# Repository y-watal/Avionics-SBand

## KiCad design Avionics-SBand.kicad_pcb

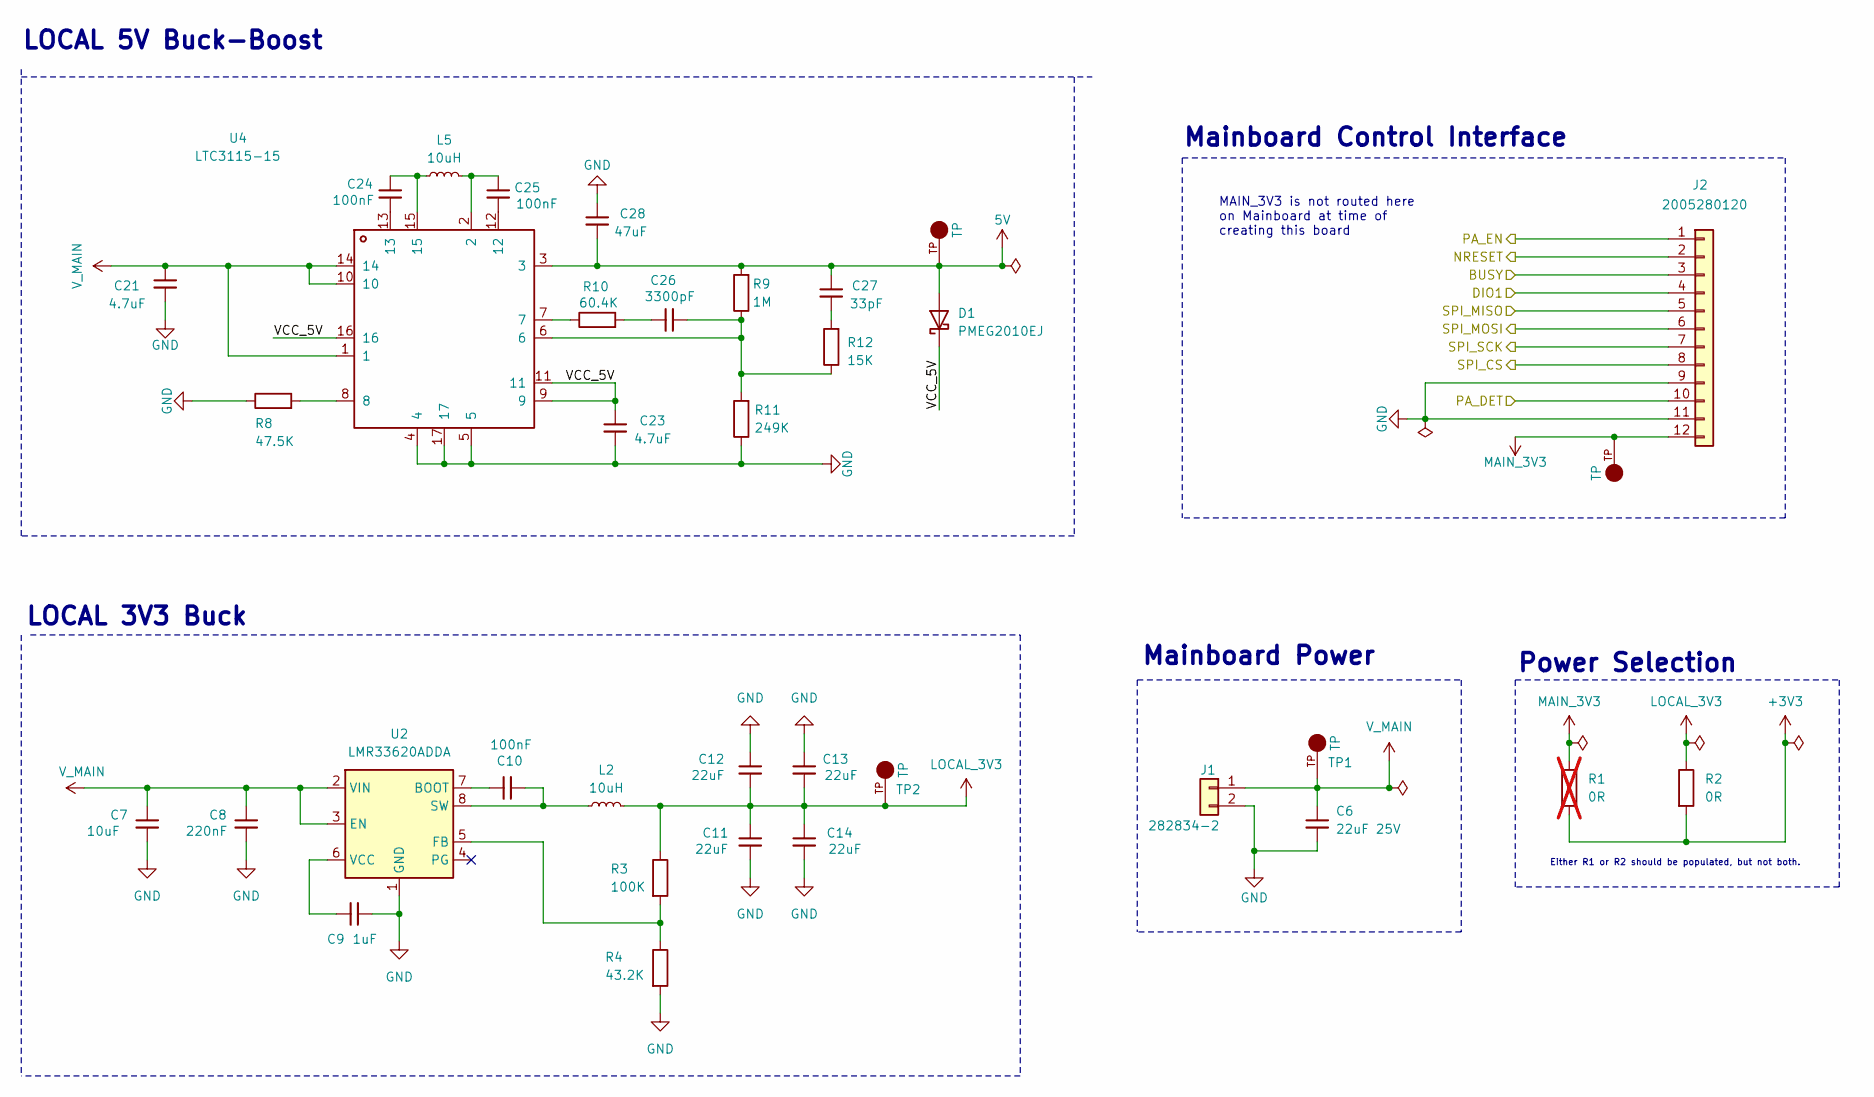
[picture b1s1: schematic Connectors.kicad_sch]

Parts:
C6: 22uF 25V; C_1210_3225Metric
C7: 10uF; C_1210_3225Metric
C8: 220nF; C_0603_1608Metric
C9: 1uF; C_0603_1608Metric
C10, C24, C25: 100nF; C_0603_1608Metric
C11, C12, C13, C14: 22uF; C_1206_3216Metric
C21, C23: 4.7uF; C_0603_1608Metric
C26: 3300pF; C_0603_1608Metric
C27: 33pF; C_0603_1608Metric
C28: 47uF; C_1206_3216Metric
D1: PMEG2010EJ; D_SOD-323F
J1: 282834-2; TE_282834-2; MPN 282834-2; Digikey PN A98333-ND
J2: 2005280120; Molex_200528-0120_1x12-1MP_P1.00mm_Horizontal
L2, L5: 10uH; L_Bourns_SRP7028A_7.3x6.6mm
R1: 0R; R_1206_3216Metric; not fitted
R2: 0R; R_1206_3216Metric
R3: 100K; R_0603_1608Metric
R4: 43.2K; R_0603_1608Metric
R8: 47.5K; R_0603_1608Metric
R9: 1M; R_0603_1608Metric
R10: 60.4K; R_0603_1608Metric
R11: 249K; R_0603_1608Metric
R12: 15K; R_0603_1608Metric
TP1, TP2, TP10, TP17: TP; KEYSTONE_5001; MPN 5001; Digikey PN 36-5001-ND
U2: LMR33620ADDA; Texas_HSOP-8-1EP_3.9x4.9mm_P1.27mm_ThermalVias
U4: LTC3115-15; DFN-16-1EP_4x5mm_P0.5mm_EP2.44x4.34mm

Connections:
5V: C27.1, C28.1, D1.2 (A), R9.2, TP10.TP, U4.3; also elsewhere on the board
+3V3: R1.2, R2.2; also elsewhere on the board
/Connectors/VCC_5V: C23.1, D1.1 (K), U4.9, U4.11, U4.16
/PA_to_Antenna/PA_DET: J2.10; also elsewhere on the board
/PA_to_Antenna/PA_EN: J2.1; also elsewhere on the board
/SX1280/BUSY: J2.3; also elsewhere on the board
/SX1280/DIO1: J2.4; also elsewhere on the board
/SX1280/NRESET: J2.2; also elsewhere on the board
/SX1280/SPI_CS: J2.8; also elsewhere on the board
/SX1280/SPI_MISO: J2.5; also elsewhere on the board
/SX1280/SPI_MOSI: J2.6; also elsewhere on the board
/SX1280/SPI_SCK: J2.7; also elsewhere on the board
GND: C6.2, C7.1, C8.1, C9.1, C11.1, C12.1, C13.1, C14.1, C21.1, C23.2, C28.2, J1.2, J2.9, J2.11, R4.2, R8.1, R11.1, U2.1 (GND), U2.9 (GND), U4.4, U4.5, U4.17; also elsewhere on the board
LOCAL_3V3: C11.2, C12.2, C13.2, C14.2, L2.2, R2.1, R3.1, TP2.TP
MAIN_3V3: J2.12, R1.1, TP17.TP
unnamed: C24.1, U4.13
unnamed: C24.2, L5.1, U4.15
unnamed: C25.1, L5.2, U4.2
unnamed: C25.2, U4.12
unnamed: C26.1, R10.2
unnamed: C26.2, R9.1, R11.2, R12.1, U4.6
unnamed: C27.2, R12.2
unnamed: R8.2, U4.8
unnamed: R10.1, U4.7
unnamed: C10.1, U2.7 (BOOT)
unnamed: R3.2, R4.1, U2.5 (FB)
unnamed: C10.2, L2.1, U2.8 (SW)
unnamed: C9.2, U2.6 (VCC)
V_MAIN: C6.1, C7.2, C8.2, C21.2, J1.1, TP1.TP, U2.2 (VIN), U2.3 (EN), U4.1, U4.10, U4.14

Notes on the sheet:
LOCAL 3V3 Buck
Either R1 or R2 should be populated, but not both.
Mainboard Control Interface
LOCAL 5V Buck-Boost
Mainboard Power
Power Selection
MAIN_3V3 is not routed here on Mainboard at time of creating this board

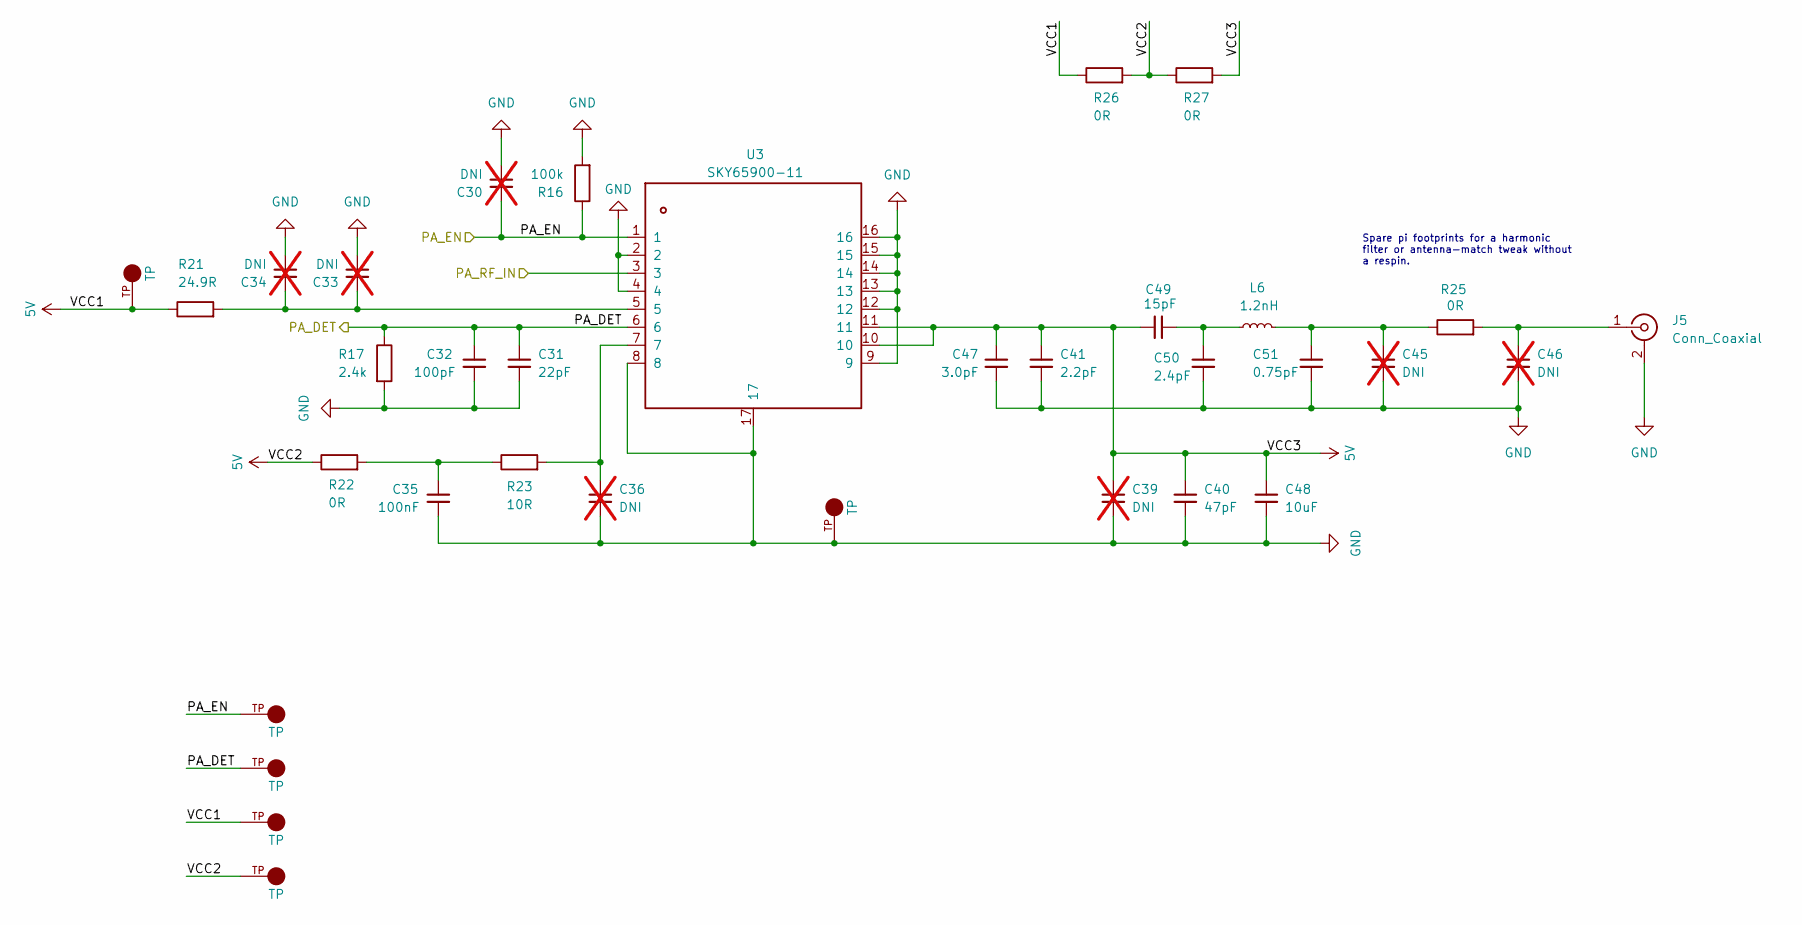
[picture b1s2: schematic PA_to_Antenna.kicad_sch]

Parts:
C30, C33, C34, C36, C39, C45, C46: DNI; C_0402_1005Metric; not fitted
C31: 22pF; C_0402_1005Metric
C32: 100pF; C_0402_1005Metric
C35: 100nF; C_0402_1005Metric
C40: 47pF; C_0402_1005Metric
C41: 2.2pF; C_0402_1005Metric
C47: 3.0pF; C_0402_1005Metric
C48: 10uF; C_0603_1608Metric
C49: 15pF; C_0402_1005Metric
C50: 2.4pF; C_0402_1005Metric
C51: 0.75pF; C_0402_1005Metric
J5: Conn_Coaxial; WR-MMCX_Wuerth_66012102111404_Vertical
L6: 1.2nH; L_0402_1005Metric
R16: 100k; R_0603_1608Metric
R17: 2.4k; R_0402_1005Metric
R21: 24.9R; R_0402_1005Metric
R22, R25, R26, R27: 0R; R_0402_1005Metric
R23: 10R; R_0402_1005Metric
TP11, TP13, TP14, TP15, TP16, TP18: TP; KEYSTONE_5001; MPN 5001; Digikey PN 36-5001-ND
U3: SKY65900-11; VQFN-16_L4_0-W4_0-P0_65-BL-EP2_4_SKY65900-11_C1870175

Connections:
5V: C39.1, C40.1, C41.1, C47.1, C48.1, C49.1, R21.1, R22.1, R26.1, R26.2, R27.1, R27.2, TP14.TP, TP15.TP, TP16.TP, U3.10, U3.11; also elsewhere on the board
/PA_to_Antenna/PA_DET: C31.1, C32.1, R17.1, TP13.TP, U3.6; also elsewhere on the board
/PA_to_Antenna/PA_EN: C30.1, R16.1, TP11.TP, U3.1; also elsewhere on the board
/PA_to_Antenna/PA_RF_IN: U3.3; also elsewhere on the board
GND: C30.2, C31.2, C32.2, C33.2, C34.2, C35.2, C36.2, C39.2, C40.2, C41.2, C45.2, C46.2, C47.2, C48.2, C50.2, C51.2, J5.2 (Ext), R16.2, R17.2, TP18.TP, U3.2, U3.4, U3.8, U3.9, U3.12, U3.13, U3.14, U3.15, U3.16, U3.17; also elsewhere on the board
unnamed: C33.1, C34.1, R21.2, U3.5
unnamed: C35.1, R22.2, R23.1
unnamed: C36.1, R23.2, U3.7
unnamed: C45.1, C51.1, L6.2, R25.1
unnamed: C49.2, C50.1, L6.1
unnamed: C46.1, J5.1 (In), R25.2

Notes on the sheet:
Spare pi footprints for a harmonic filter or antenna-match tweak without a respin.

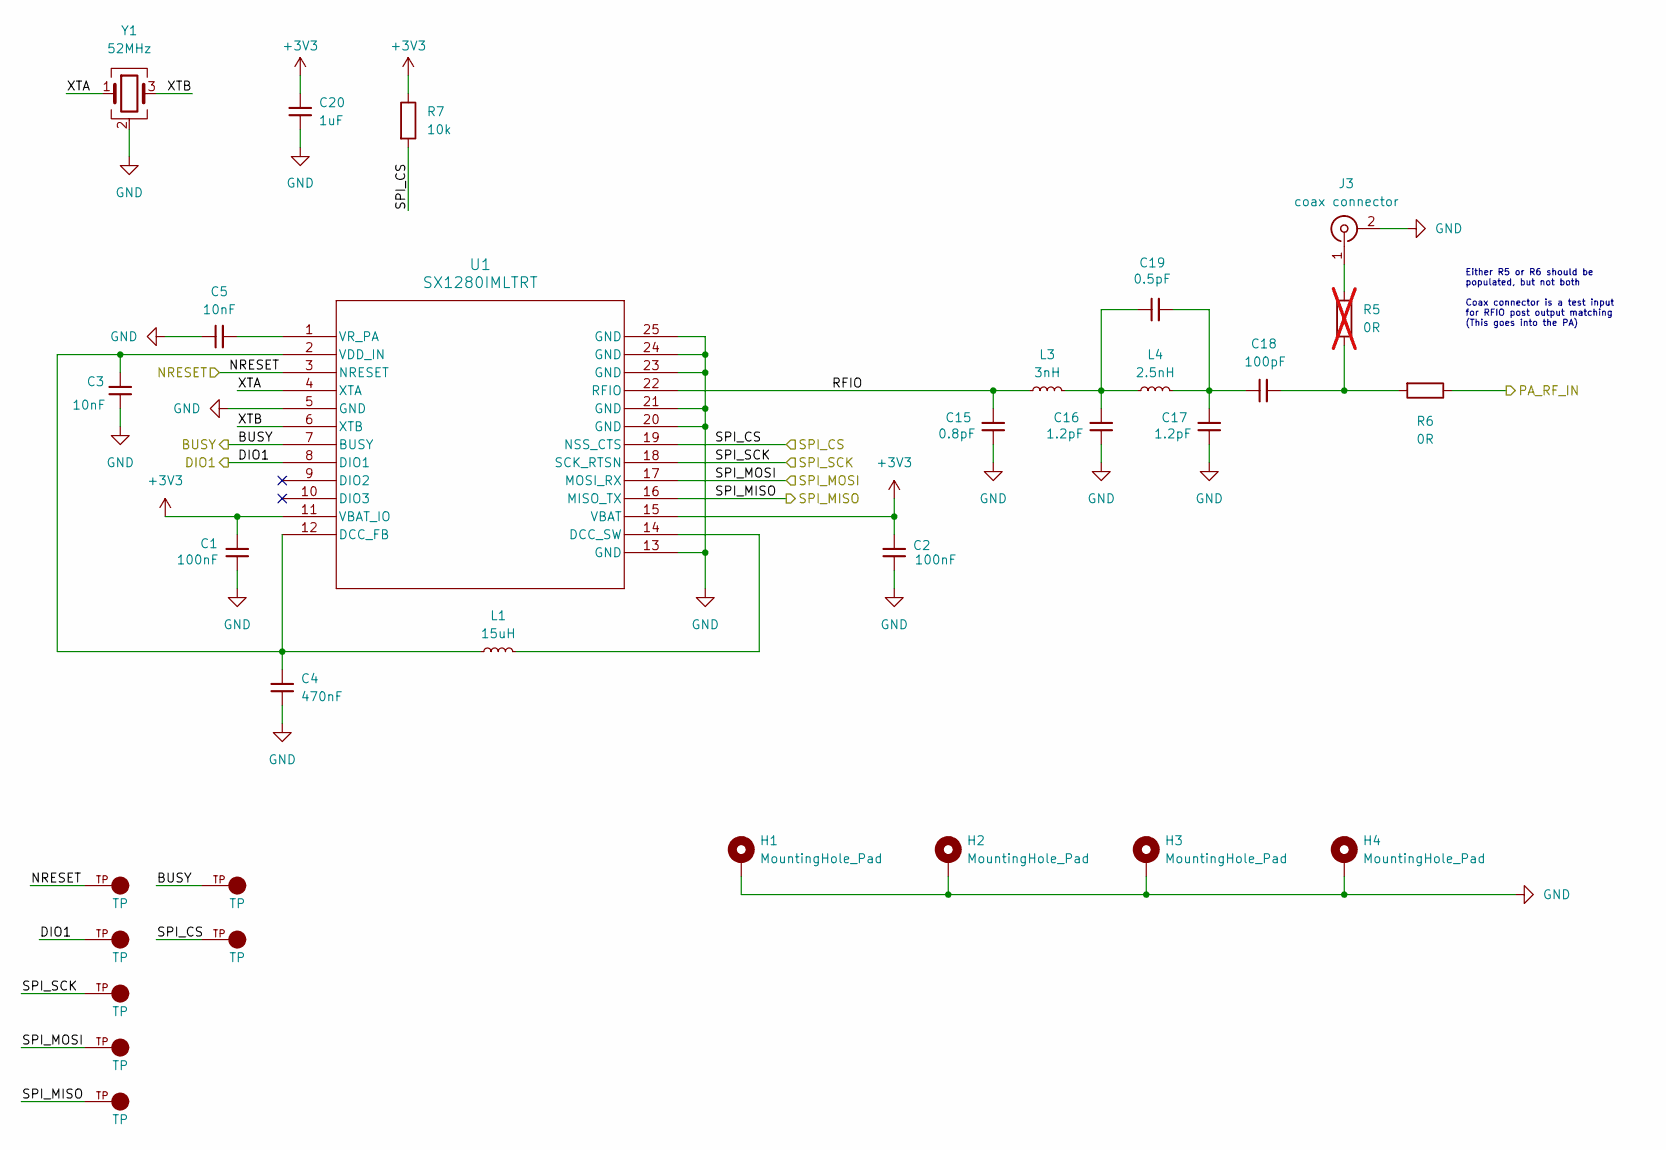
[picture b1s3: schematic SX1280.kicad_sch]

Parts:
C1, C2: 100nF; C_0402_1005Metric
C3, C5: 10nF; C_0402_1005Metric
C4: 470nF; C_0402_1005Metric
C15: 0.8pF; C_0402_1005Metric
C16, C17: 1.2pF; C_0402_1005Metric
C18: 100pF; C_0402_1005Metric
C19: 0.5pF; C_0402_1005Metric
C20: 1uF; C_0402_1005Metric
H1, H2, H3, H4: MountingHole_Pad; MountingHole_3.2mm_M3_DIN965_Pad_TopBottom
J3: coax connector; U.FL_Hirose_U.FL-R-SMT-1_Vertical
L1: 15uH; L_0805_2012Metric
L3: 3nH; L_0402_1005Metric
L4: 2.5nH; L_0402_1005Metric
R5: 0R; R_0402_1005Metric; not fitted
R6: 0R; R_0402_1005Metric
R7: 10k; R_0402_1005Metric
TP3, TP4, TP5, TP6, TP7, TP8, TP9: TP; KEYSTONE_5001; MPN 5001; Digikey PN 36-5001-ND
U1: SX1280IMLTRT; QFN24_4X4_SEM
Y1: 52MHz; Crystal_SMD_3225-4Pin_3.2x2.5mm

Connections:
+3V3: C1.2, C2.2, C20.1, R7.1, U1.11 (VBAT_IO), U1.15 (VBAT); also elsewhere on the board
/PA_to_Antenna/PA_RF_IN: R6.1; also elsewhere on the board
/SX1280/BUSY: TP4.TP, U1.7 (BUSY); also elsewhere on the board
/SX1280/DIO1: TP5.TP, U1.8 (DIO1); also elsewhere on the board
/SX1280/NRESET: TP3.TP, U1.3 (NRESET); also elsewhere on the board
/SX1280/RFIO: C15.2, L3.1, U1.22 (RFIO)
/SX1280/SPI_CS: R7.2, TP6.TP, U1.19 (NSS_CTS); also elsewhere on the board
/SX1280/SPI_MISO: TP9.TP, U1.16 (MISO_TX); also elsewhere on the board
/SX1280/SPI_MOSI: TP8.TP, U1.17 (MOSI_RX); also elsewhere on the board
/SX1280/SPI_SCK: TP7.TP, U1.18 (SCK_RTSN); also elsewhere on the board
/SX1280/XTA: U1.4 (XTA), Y1.1
/SX1280/XTB: U1.6 (XTB), Y1.3
GND: C1.1, C2.1, C3.2, C4.2, C5.2, C15.1, C16.1, C17.1, C20.2, H1.1 (1_1), H2.1 (1_1), H3.1 (1_1), H4.1 (1_1), J3.2 (Ext), U1.5 (GND), U1.13 (GND), U1.20 (GND), U1.21 (GND), U1.23 (GND), U1.24 (GND), U1.25 (GND), Y1.2 (G), Y1.4 (G); also elsewhere on the board
unnamed: C16.2, C19.1, L3.2, L4.1
unnamed: C17.2, C18.1, C19.2, L4.2
unnamed: C18.2, R5.2, R6.2
unnamed: J3.1 (In), R5.1
unnamed: C3.1, C4.1, L1.1, U1.2 (VDD_IN), U1.12 (DCC_FB)
unnamed: L1.2, U1.14 (DCC_SW)
unnamed: C5.1, U1.1 (VR_PA)

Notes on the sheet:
Either R5 or R6 should be populated, but not both Coax connector is a test input for RFIO post output matching (This goes into the PA)

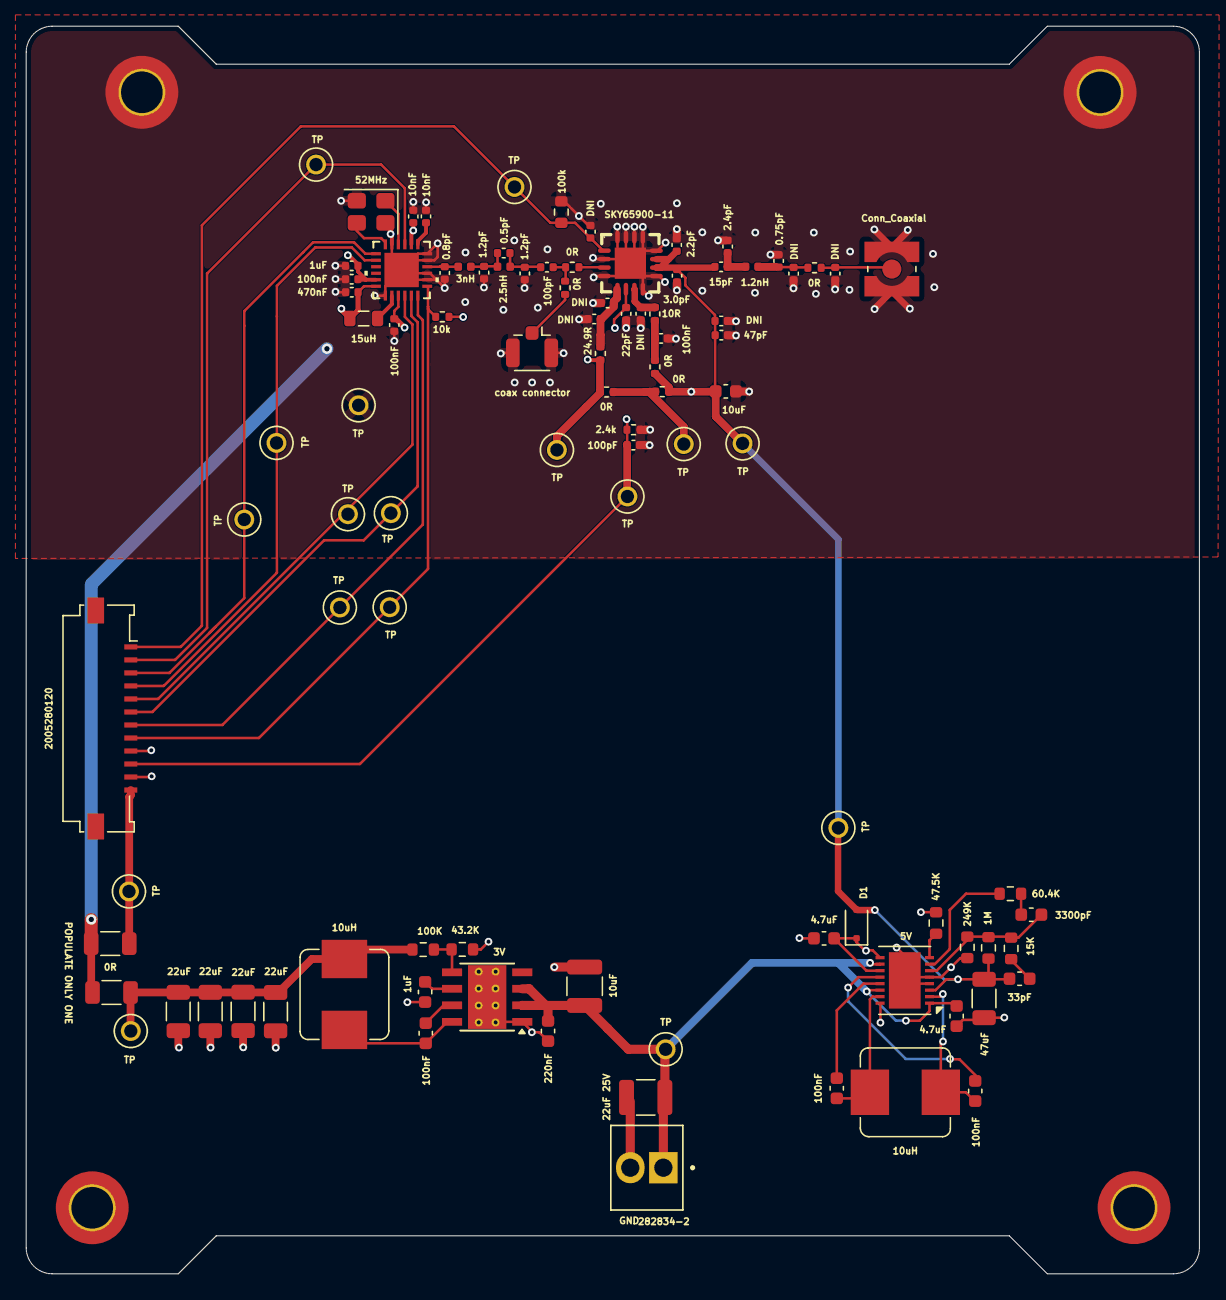
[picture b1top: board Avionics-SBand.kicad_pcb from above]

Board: 4 copper layers, 90.2 x 95.9 mm, 101 parts (0 on the bottom side), 46 nets.
